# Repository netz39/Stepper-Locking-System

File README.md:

# Stepper Locking System

Steering the key/door knob with the might of stepper motors.
See the [Wiki](https://wiki.netz39.de/projects:2022:stepper_locking_system) (german) for more details and an overview.

This is forked from https://github.com/sprenger120/StepperServo.

## Firmware
The firmware written in C++ is [here](https://github.com/netz39/Stepper-Locking-System_firmware).

## Requirements for v1.0

* control stepper motor with Trinamic IC
* hall encoder connection to get current motor state
* read motor temperature
* CAN peripherie (dedicated PCB)
* power rails are secured by two fuses, with reverse polarity/overvoltage protection
* drive syncronous addressable LEDs
* get states from door and lock
* connection to two buttons to open/close door
* switch on/off Nerdstern (outdoor lamp)

## Known issues in v1.0
* Mosfet Q1 has wrong connections for choosen part. Gate and Source are swapped.
    * can be solved by simply solder the part upside down
* the LQFP32 package of STM32G0B1KE doesn't support HSE connection
    * the internal HSI is used

## Pictures (v1.0)

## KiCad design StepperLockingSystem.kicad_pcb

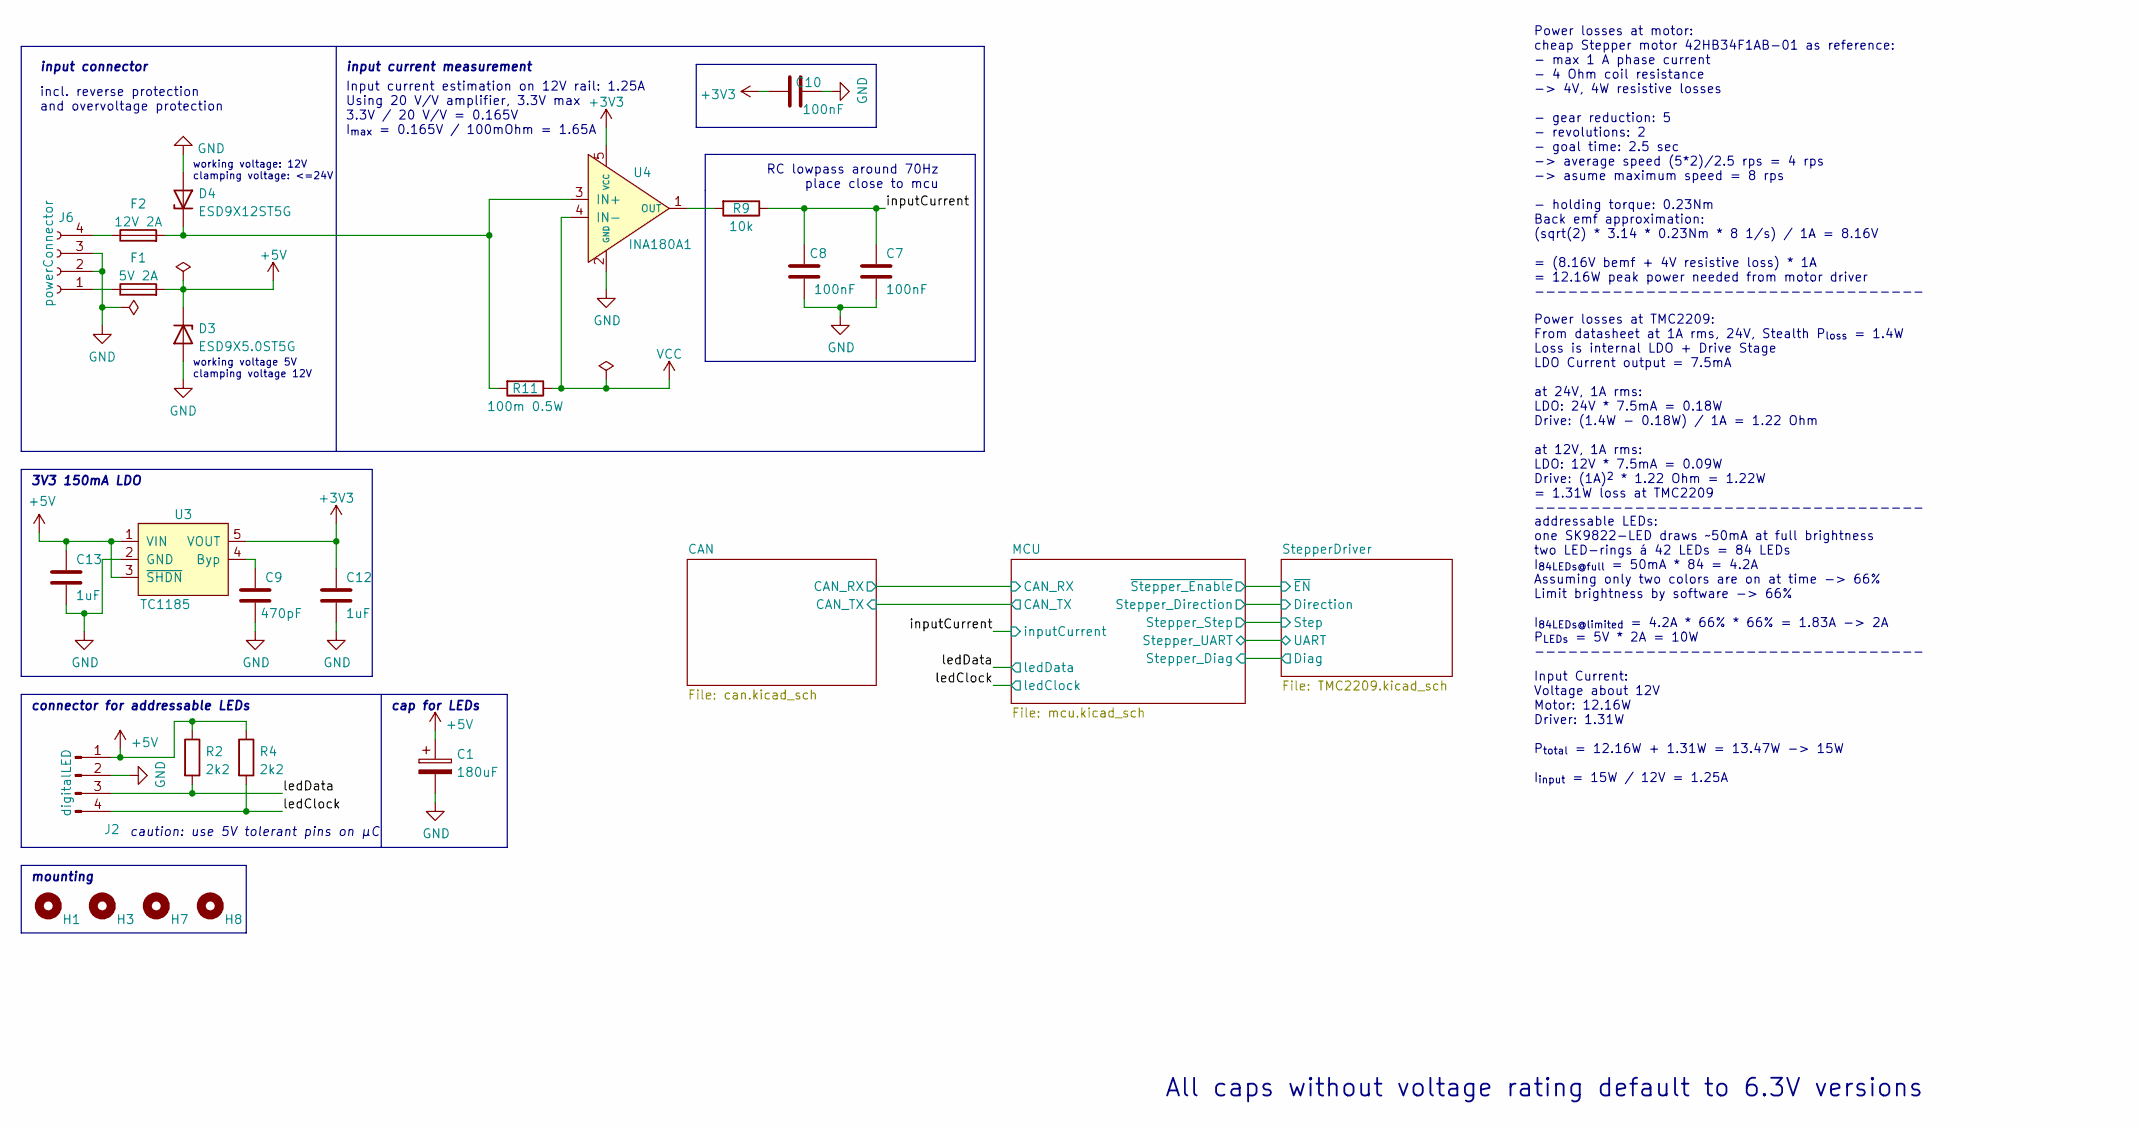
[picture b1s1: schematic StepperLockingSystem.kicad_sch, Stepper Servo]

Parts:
C1: 180uF; CP_Radial_D5.0mm_P2.50mm
C7, C8, C10: 100nF; C_0603_1608Metric
C9: 470pF; C_0603_1608Metric
C12, C13: 1uF; C_0603_1608Metric
D3: ESD9X5.0ST5G; D_SOD-923
D4: ESD9X12ST5G; D_SOD-923
F1: 5V 2A; KEYSTONE-FUSE-3557-2
F2: 12V 2A; KEYSTONE-FUSE-3557-2
H1, H3, H7, H8: MountingHole_Pad; MountingHole_3.2mm_M3_ISO7380_Keepout
J2: digitalLED; Molex_PicoBlade_53047-0410_1x04_P1.25mm_Vertical
J6: powerConnector; PhoenixContact_MSTBVA_2,5_4-G-5,08_1x04_P5.08mm_Vertical
R2, R4: 2k2; R_0603_1608Metric
R9: 10k; R_0603_1608Metric
R11: 100m 0.5W; R_0612_1632Metric
U3: TC1185; SOT-23-5
U4: INA180A1; SOT-23-5

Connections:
+5V: C1.1, C13.1, D3.1 (K), F1.2, J2.1, R2.1, R4.1, U3.1 (VIN), U3.3 (~SHDN); also elsewhere on the board
/inputCurrent: C7.1, C8.1, R9.1; also elsewhere on the board
/ledClock: J2.4, R4.2; also elsewhere on the board
/ledData: J2.3, R2.2; also elsewhere on the board
GND: C1.2, C7.2, C8.2, C9.2, C10.2, C12.2, C13.2, D3.2 (A), D4.2 (A), J2.2, J6.2, J6.3, U3.2 (GND), U4.2 (GND); also elsewhere on the board
unnamed: C9.1, U3.4 (Byp)
unnamed: D4.1 (K), F2.2, R11.2, U4.3 (IN+)
unnamed: F1.1, J6.1
unnamed: F2.1, J6.4
unnamed: R9.2, U4.1 (OUT)
VCC: R11.1, U4.4 (IN-); also elsewhere on the board

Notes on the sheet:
All caps without voltage rating default to 6.3V versions
caution: use 5V tolerant pins on µC
working voltage: 12V clamping voltage: <=24V
Input current estimation on 12V rail: 1.25A Using 20 V/V amplifier, 3.3V max 3.3V / 20 V/V = 0.165V I_{max} = 0.165V / 100mOhm = 1.65A
Power losses at TMC2209: From datasheet at 1A rms, 24V, Stealth P_{loss} = 1.4W Loss is internal LDO + Drive Stage LDO Current output = 7.5mA at 24V, 1A rms: LDO: 24V * 7.5mA = 0.18W Drive: (1.4W - 0.18W) / 1A = 1.22 Ohm at 12V, 1A rms: LDO: 12V * 7.5mA = 0.09W Drive: (1A)^{2} * 1.22 Ohm = 1.22W = 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
RC lowpass around 70Hz place close to mcu
working voltage 5V clamping voltage 12V
input connector
addressable LEDs: one SK9822-LED draws ~50mA at full brightness two LED-rings á 42 LEDs = 84 LEDs I_{84LEDs@full} = 50mA * 84 = 4.2A Assuming only two colors are on at time -> 66% Limit brightness by software -> 66% I_{84LEDs@limited} = 4.2A * 66% * 66% = 1.83A -> 2A P_{LEDs} = 5V * 2A = 10W ------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
3V3 150mA LDO
connector for addressable LEDs
input current measurement
cap for LEDs
incl. reverse protection and overvoltage protection
mounting
Input Current: Voltage about 12V Motor: 12.16W Driver: 1.31W P_{total} = 12.16W + 1.31W = 13.47W -> 15W I_{input} = 15W / 12V = 1.25A
Power losses at motor: cheap Stepper motor 42HB34F1AB-01 as reference: - max 1 A phase current - 4 Ohm coil resistance -> 4V, 4W resistive losses - gear reduction: 5 - revolutions: 2 - goal time: 2.5 sec -> average speed (5*2)/2.5 rps = 4 rps -> asume maximum speed = 8 rps - holding torque: 0.23Nm 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

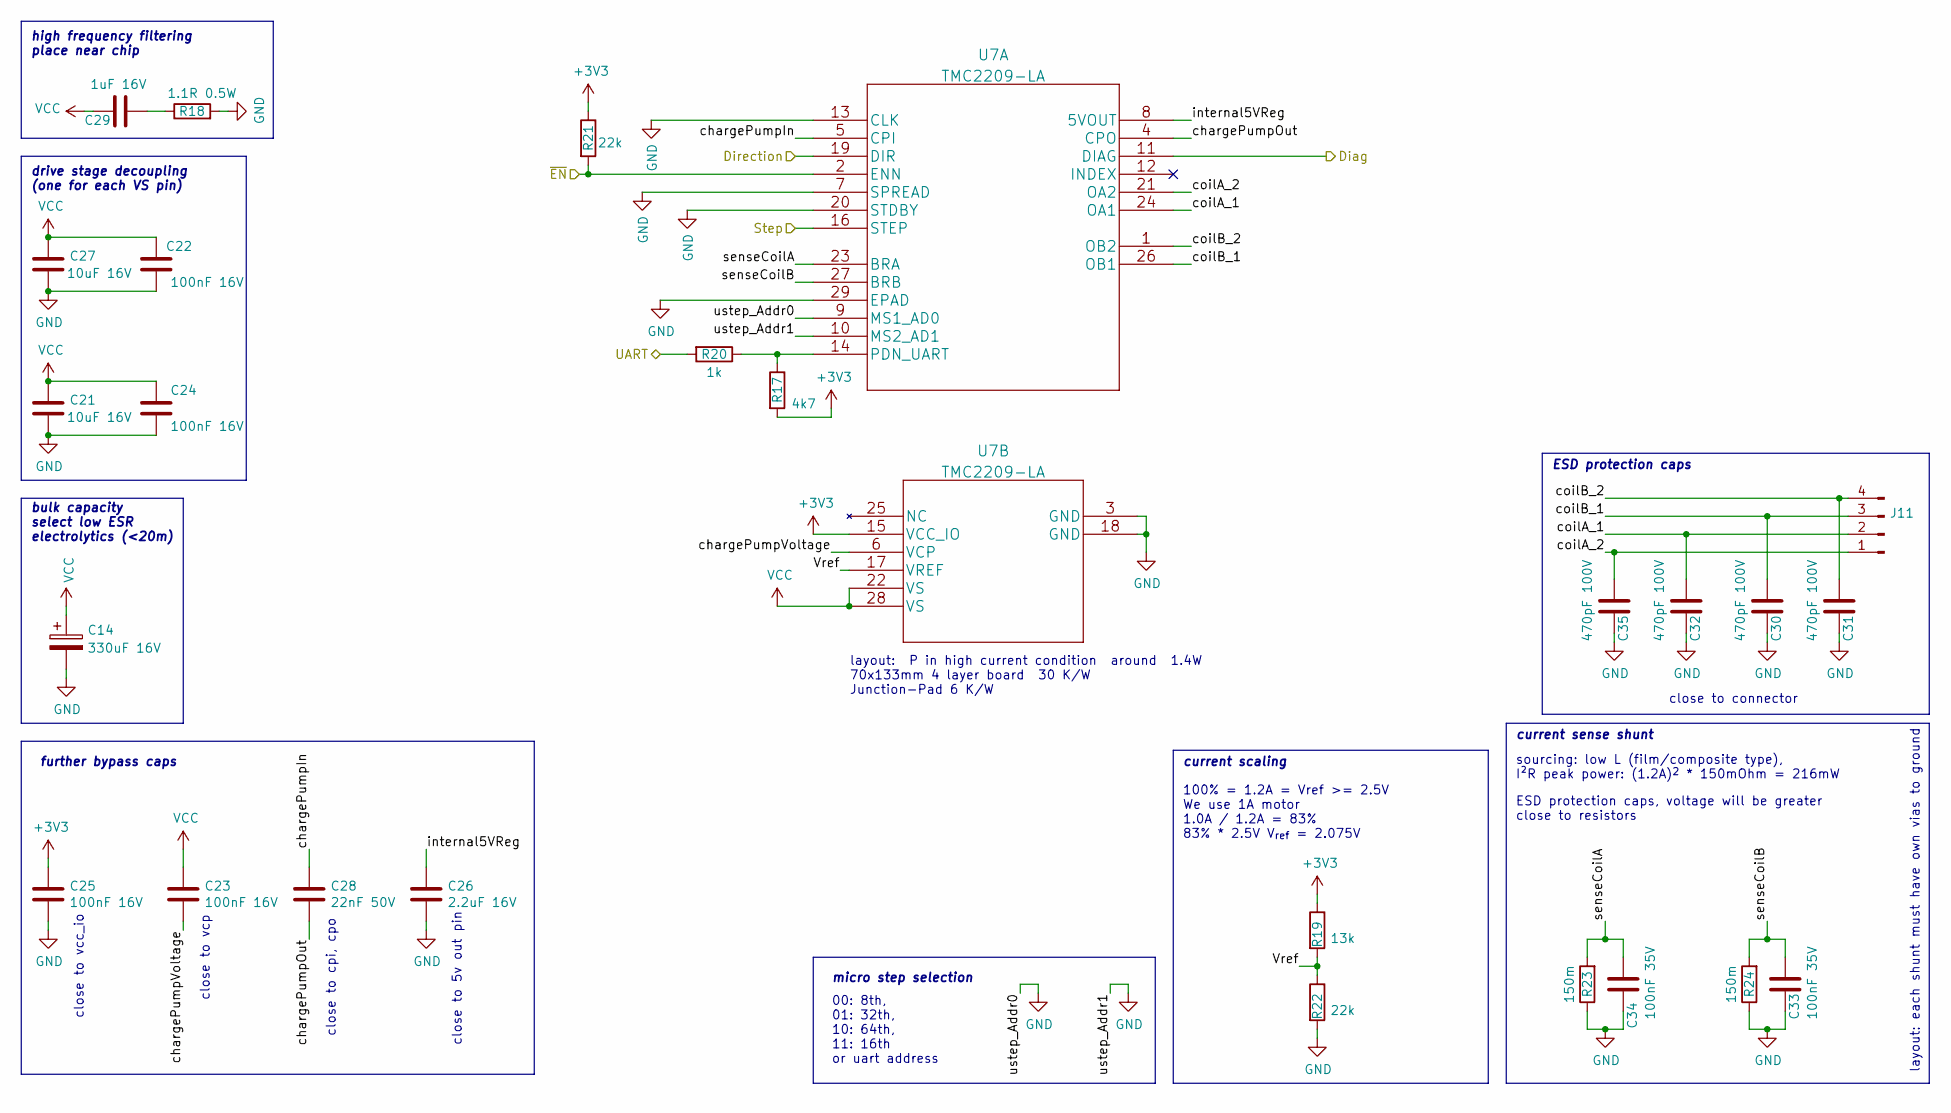
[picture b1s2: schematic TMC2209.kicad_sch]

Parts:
C14: 330uF 16V; CP_Elec_10x10.5
C21, C27: 10uF 16V; C_1206_3216Metric
C22, C23, C24, C25: 100nF 16V; C_0603_1608Metric
C26: 2.2uF 16V; C_0603_1608Metric
C28: 22nF 50V; C_0603_1608Metric
C29: 1uF 16V; C_0603_1608Metric
C30, C31, C32, C35: 470pF 100V; C_0603_1608Metric
C33, C34: 100nF 35V; C_0603_1608Metric
J11: Stepper; JST_XH_B4B-XH-A_1x04_P2.50mm_Vertical
R17: 4k7; R_0603_1608Metric
R18: 1.1R 0.5W; R_0805_2012Metric
R19: 13k; R_0603_1608Metric
R20: 1k; R_0603_1608Metric
R21, R22: 22k; R_0603_1608Metric
R23, R24: 150m; R_0612_1632Metric
U7: TMC2209-LA; QFN-28-1EP_5x5mm_P0.5mm_EP3.35x3.35mm_ThermalVias

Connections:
/MCU/Stepper_Diag: U7.11 (DIAG); also elsewhere on the board
/MCU/Stepper_Direction: U7.19 (DIR); also elsewhere on the board
/MCU/Stepper_Step: U7.16 (STEP); also elsewhere on the board
/MCU/Stepper_UART: R20.2; also elsewhere on the board
/MCU/~Stepper_Enable: R21.2, U7.2 (ENN); also elsewhere on the board
/StepperDriver/Vref: R19.2, R22.1, U7.17 (VREF)
/StepperDriver/chargePumpIn: C28.1, U7.5 (CPI)
/StepperDriver/chargePumpOut: C28.2, U7.4 (CPO)
/StepperDriver/chargePumpVoltage: C23.2, U7.6 (VCP)
/StepperDriver/coilA_1: C32.1, J11.2, U7.24 (OA1); also elsewhere on the board
/StepperDriver/coilA_2: C35.1, J11.1, U7.21 (OA2); also elsewhere on the board
/StepperDriver/coilB_1: C30.1, J11.3, U7.26 (OB1); also elsewhere on the board
/StepperDriver/coilB_2: C31.1, J11.4, U7.1 (OB2); also elsewhere on the board
/StepperDriver/internal5VReg: C26.1, U7.8 (5VOUT)
/StepperDriver/senseCoilA: C34.1, R23.2, U7.23 (BRA)
/StepperDriver/senseCoilB: C33.1, R24.2, U7.27 (BRB)
GND: C14.2, C21.2, C22.2, C24.2, C25.2, C26.2, C27.2, C30.2, C31.2, C32.2, C33.2, C34.2, C35.2, R18.2, R22.2, R23.1, R24.1, U7.3 (GND), U7.7 (SPREAD), U7.9 (MS1_AD0), U7.10 (MS2_AD1), U7.13 (CLK), U7.18 (GND), U7.20 (STDBY), U7.29 (EPAD); also elsewhere on the board
unnamed: C29.2, R18.1
unnamed: R17.1, R20.1, U7.14 (PDN_UART)
VCC: C14.1, C21.1, C22.1, C23.1, C24.1, C27.1, C29.1, U7.22 (VS), U7.28 (VS); also elsewhere on the board

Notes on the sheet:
layout: each shunt must have own vias to ground
100% = 1.2A = Vref >= 2.5V We use 1A motor 1.0A / 1.2A = 83% 83% * 2.5V V_{ref} = 2.075V
close to connector
close to vcc_io
bulk capacity select low ESR electrolytics (<20m)
drive stage decoupling (one for each VS pin)
current scaling
further bypass caps
micro step selection
ESD protection caps, voltage will be greater close to resistors
sourcing: low L (film/composite type), I²R peak power: (1.2A)^{2} * 150mOhm = 216mW
close to vcp
current sense shunt
close to cpi, cpo
00: 8th, 01: 32th, 10: 64th, 11: 16th or uart address
ESD protection caps
layout: P in high current condition around 1.4W 70x133mm 4 layer board 30 K/W Junction-Pad 6 K/W
high frequency filtering place near chip
close to 5v out pin

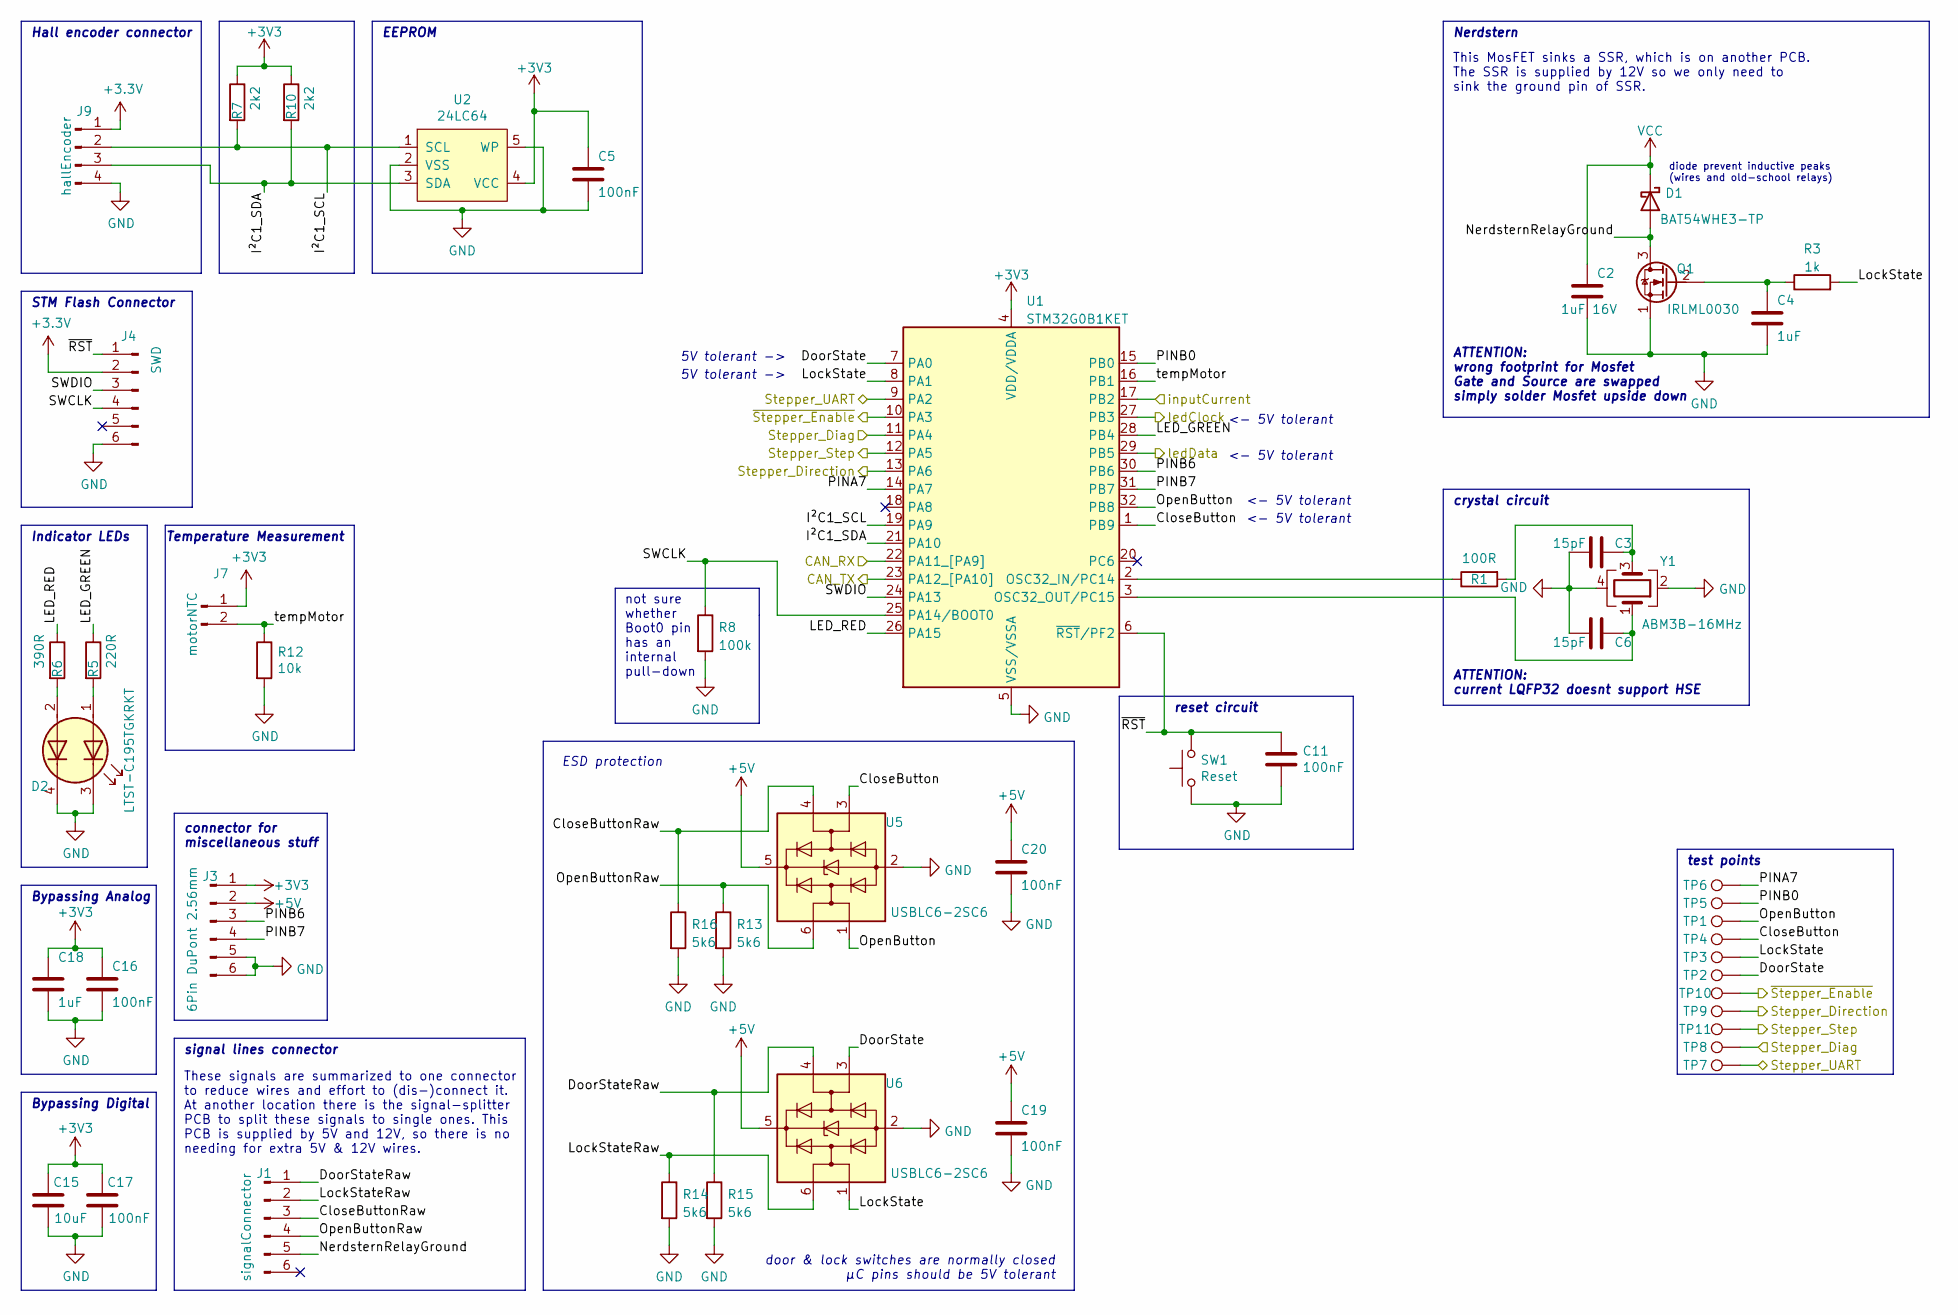
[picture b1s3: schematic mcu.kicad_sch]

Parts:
C2: 1uF 16V; C_0603_1608Metric
C3, C6: 15pF; C_0603_1608Metric
C4, C18: 1uF; C_0603_1608Metric
C5, C11, C16, C17, C19, C20: 100nF; C_0603_1608Metric
C15: 10uF; C_1206_3216Metric
D1: BAT54WHE3-TP; D_SOD-123
D2: LTST-C195TGKRKT; LED_LiteOn_LTST-C195TGKRKT
J1: signalConnector; Molex_PicoBlade_53047-0610_1x06_P1.25mm_Vertical
J3: 6Pin DuPont 2.56mm; PinHeader_2x03_P2.54mm_Vertical
J4: SWD; Molex_PicoBlade_53047-0610_1x06_P1.25mm_Vertical
J7: motorNTC; Molex_PicoBlade_53047-0210_1x02_P1.25mm_Vertical
J9: hallEncoder; Molex_PicoBlade_53047-0410_1x04_P1.25mm_Vertical
Q1: IRLML0030; SOT-23
R1: 100R; R_0603_1608Metric
R3: 1k; R_0603_1608Metric
R5: 220R; R_0603_1608Metric
R6: 390R; R_0603_1608Metric
R7, R10: 2k2; R_0603_1608Metric
R8: 100k; R_0603_1608Metric
R12: 10k; R_0603_1608Metric
R13, R14, R15, R16: 5k6; R_0603_1608Metric
SW1: Reset; PTS636_F-leads
TP1, TP2, TP3, TP4, TP5, TP6, TP7, TP8, TP9, TP10, TP11: TestPoint; TestPoint_Pad_D2.0mm
U1: STM32G0B1KET; LQFP-32_7x7mm_P0.8mm
U2: 24LC64; SOT-23-5
U5, U6: USBLC6-2SC6; SOT-23-6
Y1: ABM3B-16MHz; Crystal_SMD_Abracon_ABM3B-4Pin_5.0x3.2mm

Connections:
+5V: C19.2, C20.2, J3.2, U5.5 (VBUS), U6.5 (VBUS); also elsewhere on the board
/CAN/CAN_RX: U1.22 (PA11_[PA9]); also elsewhere on the board
/CAN/CAN_TX: U1.23 (PA12_[PA10]); also elsewhere on the board
/MCU/CloseButton: TP4.1, U1.1 (PB9), U5.3 (I/O2)
/MCU/CloseButtonRaw: J1.3, R16.1, U5.4 (I/O2)
/MCU/DoorState: TP2.1, U1.7 (PA0), U6.3 (I/O2)
/MCU/DoorStateRaw: J1.1, R15.1, U6.4 (I/O2)
/MCU/I²C1_SCL: J9.2, R7.2, U1.19 (PA9), U2.1 (SCL)
/MCU/I²C1_SDA: J9.3, R10.2, U1.21 (PA10), U2.3 (SDA)
/MCU/LED_GREEN: R5.1, U1.28 (PB4)
/MCU/LED_RED: R6.1, U1.26 (PA15)
/MCU/LockState: R3.2, TP3.1, U1.8 (PA1), U6.1 (I/O1)
/MCU/LockStateRaw: J1.2, R14.1, U6.6 (I/O1)
/MCU/NerdsternRelayGround: D1.2 (A), J1.5, Q1.3 (D)
/MCU/OpenButton: TP1.1, U1.32 (PB8), U5.1 (I/O1)
/MCU/OpenButtonRaw: J1.4, R13.1, U5.6 (I/O1)
/MCU/PINA7: TP6.1, U1.14 (PA7)
/MCU/PINB0: TP5.1, U1.15 (PB0)
/MCU/PINB6: J3.3, U1.30 (PB6)
/MCU/PINB7: J3.4, U1.31 (PB7)
/MCU/SWCLK: J4.4, R8.1, U1.25 (PA14/BOOT0)
/MCU/SWDIO: J4.3, U1.24 (PA13)
/MCU/Stepper_Diag: TP8.1, U1.11 (PA4); also elsewhere on the board
/MCU/Stepper_Direction: TP9.1, U1.13 (PA6); also elsewhere on the board
/MCU/Stepper_Step: TP11.1, U1.12 (PA5); also elsewhere on the board
/MCU/Stepper_UART: TP7.1, U1.9 (PA2); also elsewhere on the board
/MCU/tempMotor: J7.2, R12.1, U1.16 (PB1)
/MCU/~RST: C11.1, J4.1, SW1.2, U1.6 (~RST/PF2)
/MCU/~Stepper_Enable: TP10.1, U1.10 (PA3); also elsewhere on the board
/inputCurrent: U1.17 (PB2); also elsewhere on the board
/ledClock: U1.27 (PB3); also elsewhere on the board
/ledData: U1.29 (PB5); also elsewhere on the board
GND: C2.2, C3.1, C4.2, C5.2, C6.1, C11.2, C15.1, C16.2, C17.1, C18.2, C19.1, C20.1, D2.3 (K1), D2.4 (K2), J3.5, J3.6, J4.6, J9.4, Q1.1 (S), R8.2, R12.2, R13.2, R14.2, R15.2, R16.2, SW1.1, U1.5 (VSS/VSSA), U2.2 (VSS), U2.5 (WP), U5.2 (GND), U6.2 (GND), Y1.2, Y1.4; also elsewhere on the board
unnamed: C3.2, R1.2, Y1.3
unnamed: C4.1, Q1.2 (G), R3.1
unnamed: C6.2, U1.3 (OSC32_OUT/PC15), Y1.1
unnamed: D2.1 (A1), R5.2
unnamed: D2.2 (A2), R6.2
unnamed: R1.1, U1.2 (OSC32_IN/PC14)
VCC: C2.1, D1.1 (K); also elsewhere on the board

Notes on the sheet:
ATTENTION: wrong footprint for Mosfet Gate and Source are swapped simply solder Mosfet upside down
5V tolerant ->
crystal circuit
Bypassing Digital
Nerdstern
Bypassing Analog
reset circuit
not sure whether Boot0 pin has an internal pull-down
diode prevent inductive peaks (wires and old-school relays)
test points
<- 5V tolerant
ESD protection
Indicator LEDs
Hall encoder connector
door & lock switches are normally closed µC pins should be 5V tolerant
connector for miscellaneous stuff
ATTENTION: current LQFP32 doesnt support HSE
This MosFET sinks a SSR, which is on another PCB. The SSR is supplied by 12V so we only need to sink the ground pin of SSR.
EEPROM
These signals are summarized to one connector to reduce wires and effort to (dis-)connect it. At another location there is the signal-splitter PCB to split these signals to single ones. This PCB is supplied by 5V and 12V, so there is no needing for extra 5V & 12V wires.
Temperature Measurement
STM Flash Connector
signal lines connector

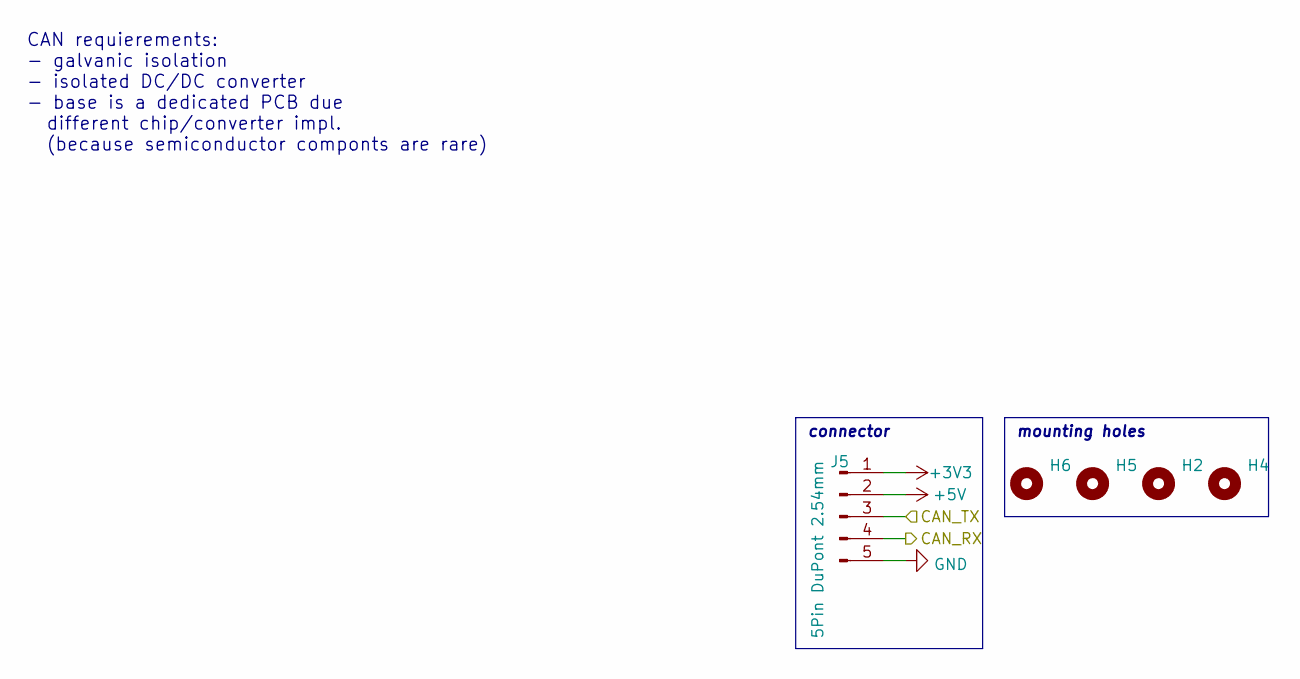
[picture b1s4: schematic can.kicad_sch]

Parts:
H2, H4, H5, H6: MountingHole_Pad; MountingHole_3.2mm_M3_ISO7380_Keepout
J5: 5Pin DuPont 2.54mm; PinHeader_1x05_P2.54mm_Vertical

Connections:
+5V: J5.2; also elsewhere on the board
/CAN/CAN_RX: J5.4; also elsewhere on the board
/CAN/CAN_TX: J5.3; also elsewhere on the board
GND: J5.5; also elsewhere on the board

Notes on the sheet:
mounting holes
CAN requierements: - galvanic isolation - isolated DC/DC converter - base is a dedicated PCB due different chip/converter impl. (because semiconductor componts are rare)
connector

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
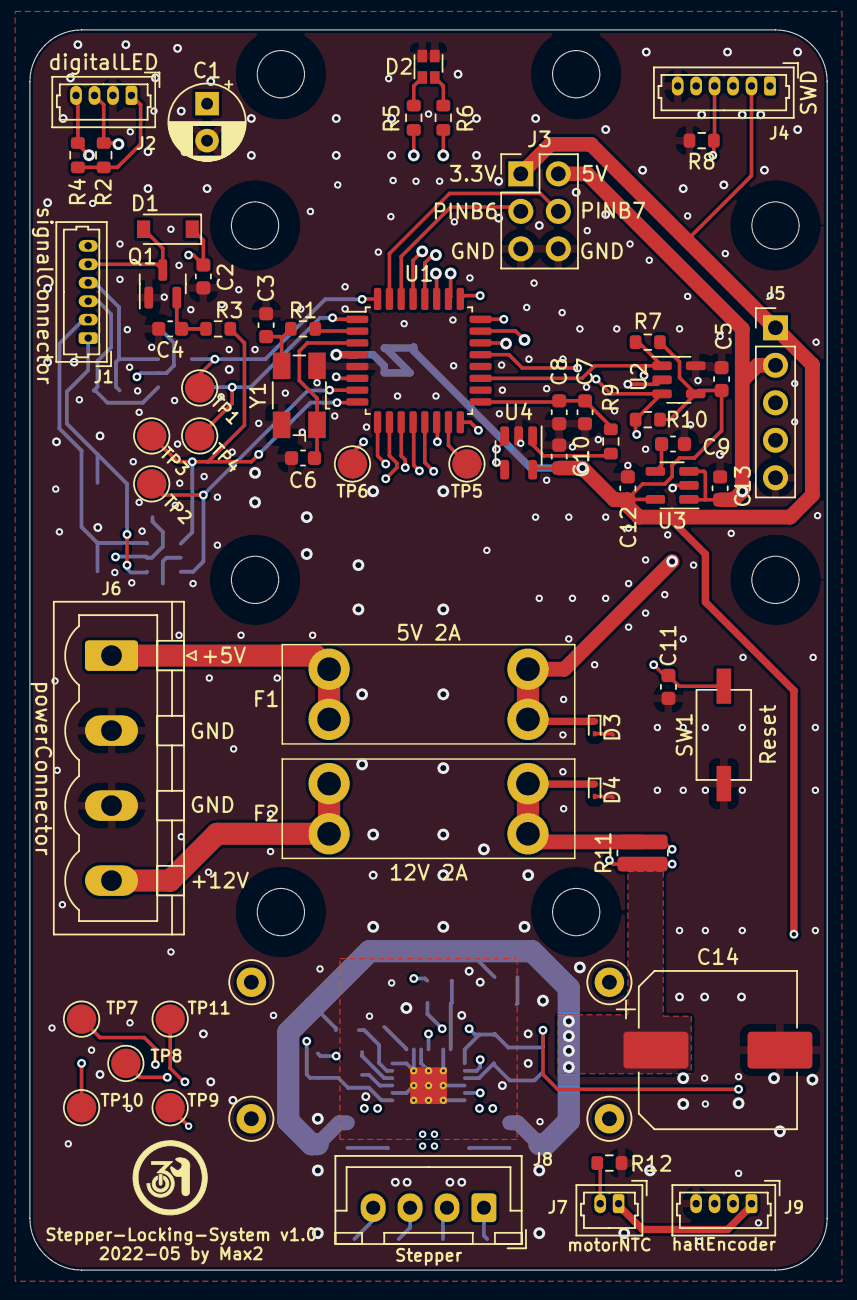
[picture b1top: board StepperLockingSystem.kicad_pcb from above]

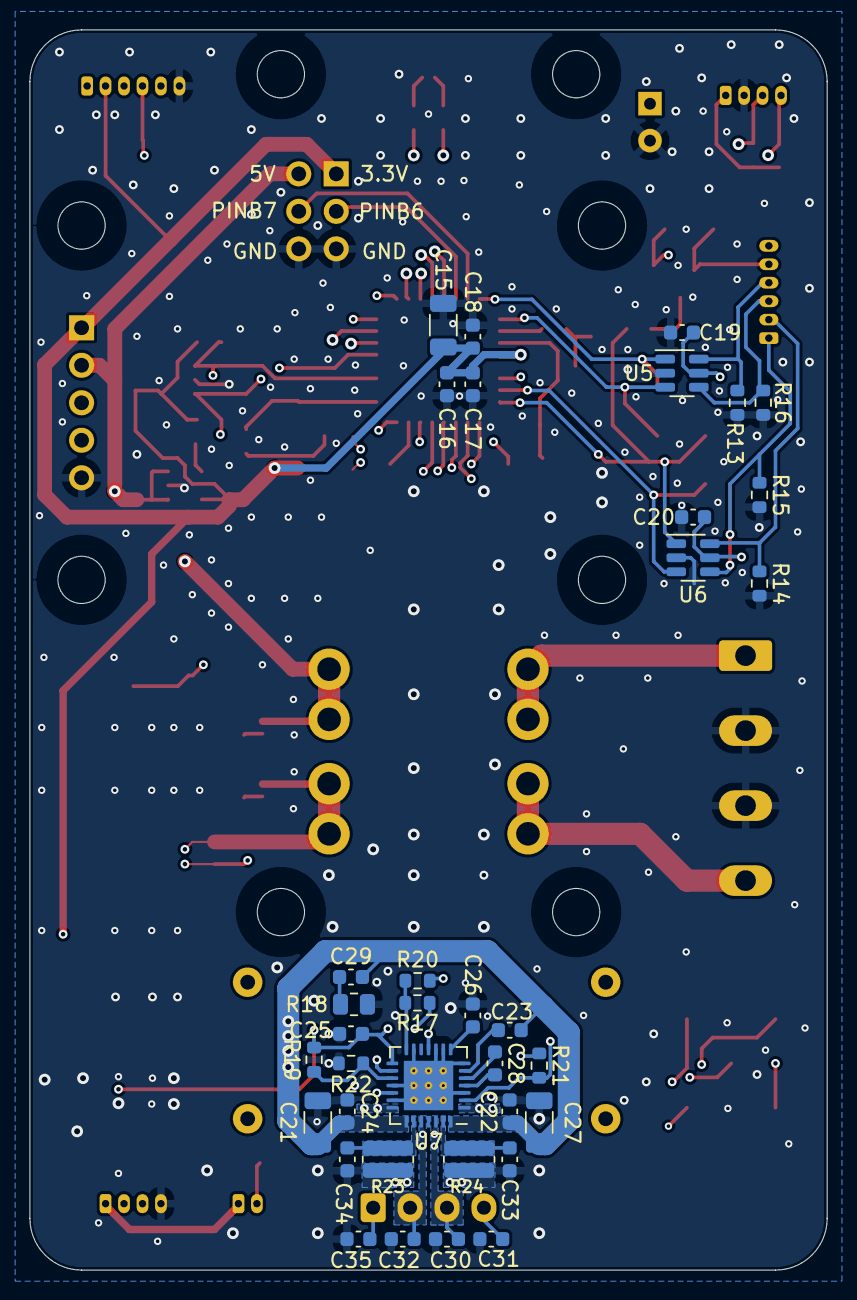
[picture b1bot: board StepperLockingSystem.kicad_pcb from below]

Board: 4 copper layers, 54.0 x 84.0 mm, 103 parts (36 on the bottom side), 59 nets.

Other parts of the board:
J8: Stepper; JST_XH_B4B-XH-A_1x04_P2.50mm_Vertical

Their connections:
/StepperDriver/coilA_1: J8.2; also elsewhere on the board
/StepperDriver/coilA_2: J8.1; also elsewhere on the board
/StepperDriver/coilB_1: J8.3; also elsewhere on the board
/StepperDriver/coilB_2: J8.4; also elsewhere on the board

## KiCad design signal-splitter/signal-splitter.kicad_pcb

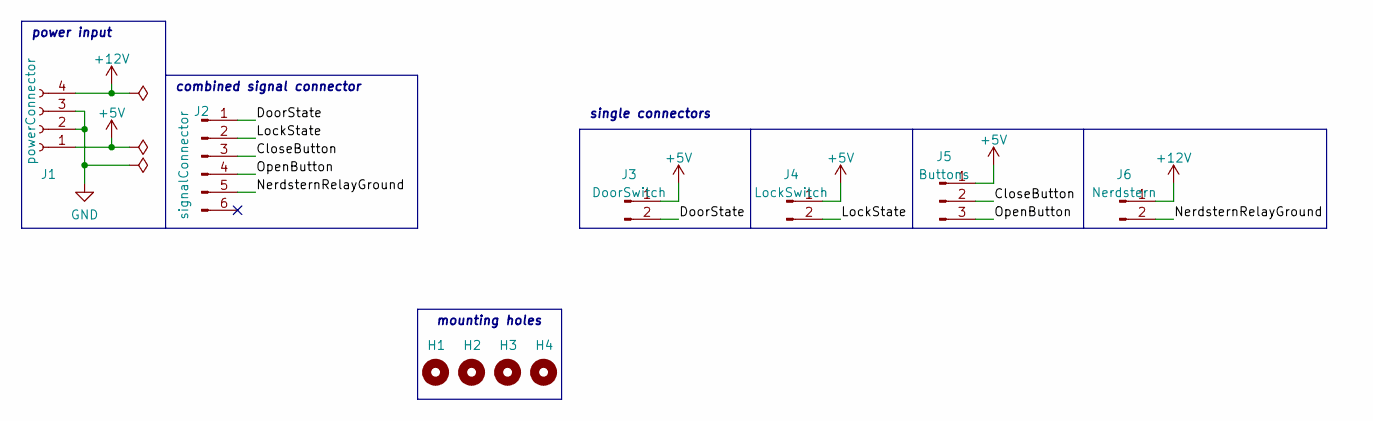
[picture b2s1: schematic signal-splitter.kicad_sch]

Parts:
H1, H2, H3, H4: MountingHole; MountingHole_3.2mm_M3_ISO14580
J1: powerConnector; PhoenixContact_MSTBA_2,5_4-G-5,08_1x04_P5.08mm_Horizontal
J2: signalConnector; Molex_PicoBlade_53047-0610_1x06_P1.25mm_Vertical
J3: DoorSwitch; Molex_PicoBlade_53047-0210_1x02_P1.25mm_Vertical
J4: LockSwitch; Molex_PicoBlade_53047-0210_1x02_P1.25mm_Vertical
J5: Buttons; Molex_PicoBlade_53047-0310_1x03_P1.25mm_Vertical
J6: Nerdstern; Molex_PicoBlade_53047-0210_1x02_P1.25mm_Vertical

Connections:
+5V: J1.1, J3.1, J4.1, J5.1
+12V: J1.4, J6.1
/CloseButton: J2.3, J5.2
/DoorState: J2.1, J3.2
/LockState: J2.2, J4.2
/NerdsternRelayGround: J2.5, J6.2
/OpenButton: J2.4, J5.3
GND: J1.2, J1.3

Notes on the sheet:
power input
single connectors
mounting holes
combined signal connector

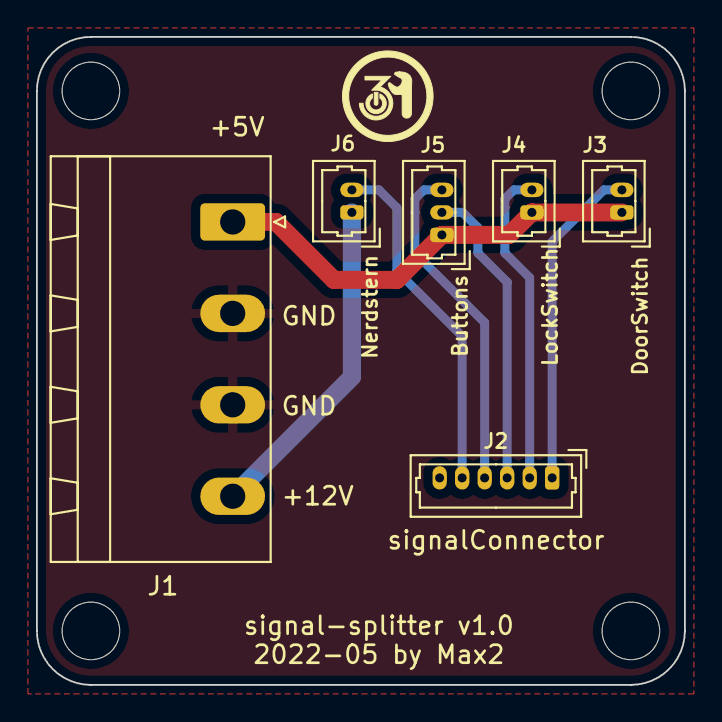
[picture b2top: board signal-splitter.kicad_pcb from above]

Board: 2 copper layers, 36.0 x 36.0 mm, 10 parts (0 on the bottom side), 8 nets.

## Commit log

2022-01-12 Clean up
2022-02-21 KiCad 6 changes
2022-02-21 Update notes
2022-04-04 Convert to new library format Remove unnecessary symbols
2022-04-04 Rename files Remove unnecessary contents
2022-04-04 Cleanup CAD, Datasheets and BOM
2022-04-04 Consolidate symbols to one libary
2022-04-04 Rename footprint folder
2022-04-04 Rearrange schematic and some cleanups Add 5V buck converter Update values for TMC2209 Add EEPROM Switch to STM32G0B1KE
2022-04-04 Small changes
2022-04-07 Annotate symbols and assign footprints
2022-04-09 [WIP] Create PCB
2022-05-10 Finish schematic
2022-05-12 Add many changes to schematic and WIP PCB
2022-05-12 Some changes to schematic
2022-05-15 Finish PCB layout
2022-05-15 Add ground plane vias
2022-05-16 Add BOM and update some values due component order
2022-05-16 Update Readme by adding images
2022-05-16 Update footprint and export step file
2022-05-17 Change positions of mounting holes to middle
2022-05-18 Add holes for heat sink
2022-05-18 Move note
2022-05-19 Add note to door/lock state switches
2022-05-22 Apply suggestions from tux: Single connector for signals Some (better) notes
2022-05-22 Change power input pin out Update exported stuffs Update ReadMe
2022-05-22 Add signal-splitter pcb
2022-05-22 Add settings for Gerber
2022-06-11 Note two known issues
2022-06-11 Update exports
2022-07-14 ReadMe: Add references
2022-12-12 Add note to fork in ReadMe
